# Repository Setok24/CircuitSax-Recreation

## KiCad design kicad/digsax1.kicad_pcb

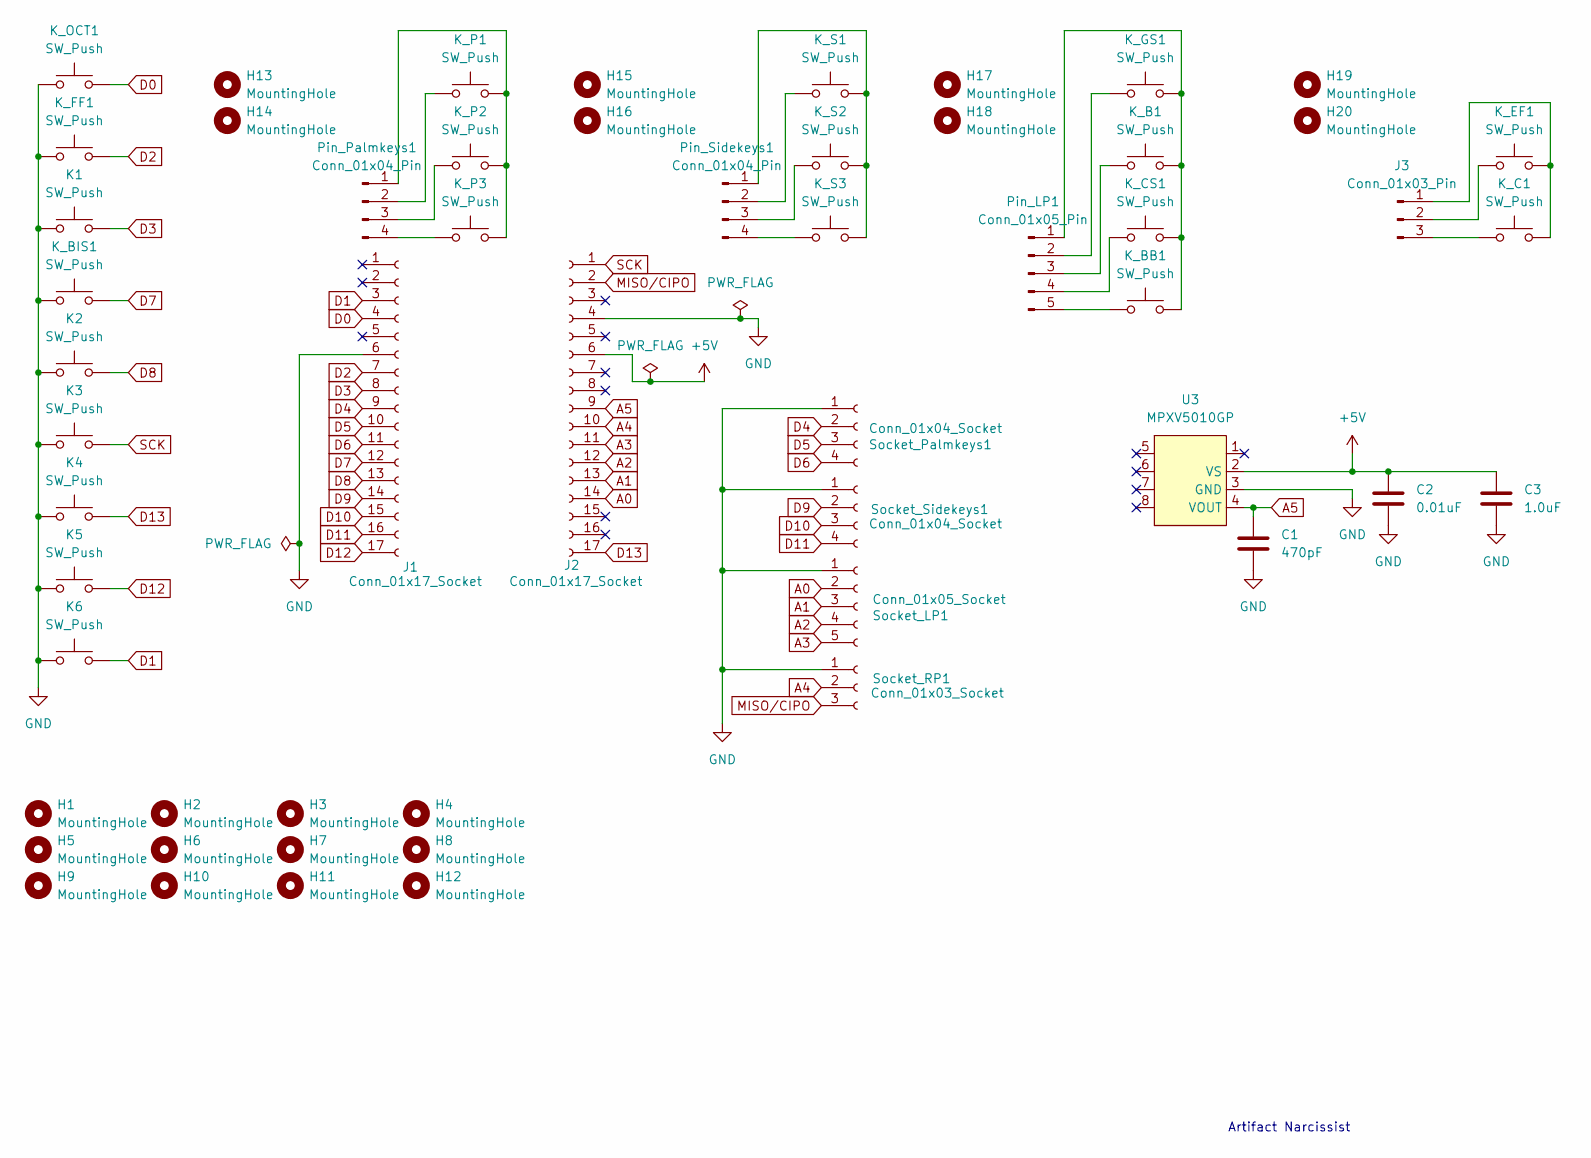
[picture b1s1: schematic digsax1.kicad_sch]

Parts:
C1: 470pF; C_0805_2012Metric
C2: 0.01uF; C_0805_2012Metric
C3: 1.0uF; C_0805_2012Metric
H1, H2, H3, H4, H5, H6, H7, H8, H9, H10, H11, H12, H13, H14, H15, H16, H17, H18, H19, H20: MountingHole; MountingHole_3.2mm_M3
J1, J2: Conn_01x17_Socket; PinSocket_1x17_P2.54mm_Vertical
J3: Conn_01x03_Pin; PinHeader_1x03_P2.54mm_Vertical
K1, K2, K3, K4, K5, K6: SW_Push; SW_Cherry_MX_1.00u_PCB
K_B1: SW_Push; SW_Cherry_MX_1.00u_PCB
K_BB1: SW_Push; SW_Cherry_MX_1.00u_PCB
K_BIS1: SW_Push; SW_Cherry_MX_1.00u_PCB
K_C1: SW_Push; SW_Cherry_MX_1.00u_PCB
K_CS1: SW_Push; SW_Cherry_MX_1.00u_PCB
K_EF1: SW_Push; SW_Cherry_MX_1.00u_PCB
K_FF1: SW_Push; SW_Cherry_MX_1.00u_PCB
K_GS1: SW_Push; SW_Cherry_MX_1.00u_PCB
K_OCT1: SW_Push; SW_Cherry_MX_1.00u_PCB
K_P1, K_P2, K_P3: SW_Push; SW_Cherry_MX_1.00u_PCB
K_S1, K_S2, K_S3: SW_Push; SW_Cherry_MX_1.00u_PCB
Pin_LP1: Conn_01x05_Pin; PinHeader_1x05_P2.54mm_Vertical
Pin_Palmkeys1: Conn_01x04_Pin; PinHeader_1x04_P2.54mm_Vertical
Pin_Sidekeys1: Conn_01x04_Pin; PinHeader_1x04_P2.54mm_Vertical
Socket_LP1: Conn_01x05_Socket; PinSocket_1x05_P2.54mm_Vertical
Socket_Palmkeys1: Conn_01x04_Socket; PinSocket_1x04_P2.54mm_Vertical
Socket_RP1: Conn_01x03_Socket; PinSocket_1x03_P2.54mm_Vertical
Socket_Sidekeys1: Conn_01x04_Socket; PinSocket_1x04_P2.54mm_Vertical
U3: MPXV5010GP; DIP-6_W7.62mm_LongPads

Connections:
+5V: C2.1, C3.1, J2.6, U3.2 (VS)
A0: J2.14, Socket_LP1.2
A1: J2.13, Socket_LP1.3
A2: J2.12, Socket_LP1.4
A3: J2.11, Socket_LP1.5
A4: J2.10, Socket_RP1.2
A5: C1.1, J2.9, U3.4 (VOUT)
D0: J1.4, K_OCT1.2
D1: J1.3, K6.2
D2: J1.7, K_FF1.2
D3: J1.8, K1.2
D4: J1.9, Socket_Palmkeys1.2
D5: J1.10, Socket_Palmkeys1.3
D6: J1.11, Socket_Palmkeys1.4
D7: J1.12, K_BIS1.2
D8: J1.13, K2.2
D9: J1.14, Socket_Sidekeys1.2
D10: J1.15, Socket_Sidekeys1.3
D11: J1.16, Socket_Sidekeys1.4
D12: J1.17, K5.2
D13: J2.17, K4.2
GND: C1.2, C2.2, C3.2, J1.6, J2.4, K1.1, K2.1, K3.1, K4.1, K5.1, K6.1, K_BIS1.1, K_FF1.1, K_OCT1.1, Socket_LP1.1, Socket_Palmkeys1.1, Socket_RP1.1, Socket_Sidekeys1.1, U3.3 (GND)
unnamed: J3.1, K_C1.2, K_EF1.2
unnamed: J3.2, K_EF1.1
unnamed: J3.3, K_C1.1
unnamed: K_B1.2, K_BB1.2, K_CS1.2, K_GS1.2, Pin_LP1.1
unnamed: K_GS1.1, Pin_LP1.2
unnamed: K_B1.1, Pin_LP1.3
unnamed: K_CS1.1, Pin_LP1.4
unnamed: K_BB1.1, Pin_LP1.5
unnamed: K_P1.2, K_P2.2, K_P3.2, Pin_Palmkeys1.1
unnamed: K_P1.1, Pin_Palmkeys1.2
unnamed: K_P2.1, Pin_Palmkeys1.3
unnamed: K_P3.1, Pin_Palmkeys1.4
unnamed: K_S1.2, K_S2.2, K_S3.2, Pin_Sidekeys1.1
unnamed: K_S1.1, Pin_Sidekeys1.2
unnamed: K_S2.1, Pin_Sidekeys1.3
unnamed: K_S3.1, Pin_Sidekeys1.4
SCK: J2.1, K3.2

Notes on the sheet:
Artifact Narcissist

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
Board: 2 copper layers, 55 parts (1 on the bottom side), 40 nets, no tracks yet.

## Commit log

2025-08-01 simplified
2025-08-01 addprogress
